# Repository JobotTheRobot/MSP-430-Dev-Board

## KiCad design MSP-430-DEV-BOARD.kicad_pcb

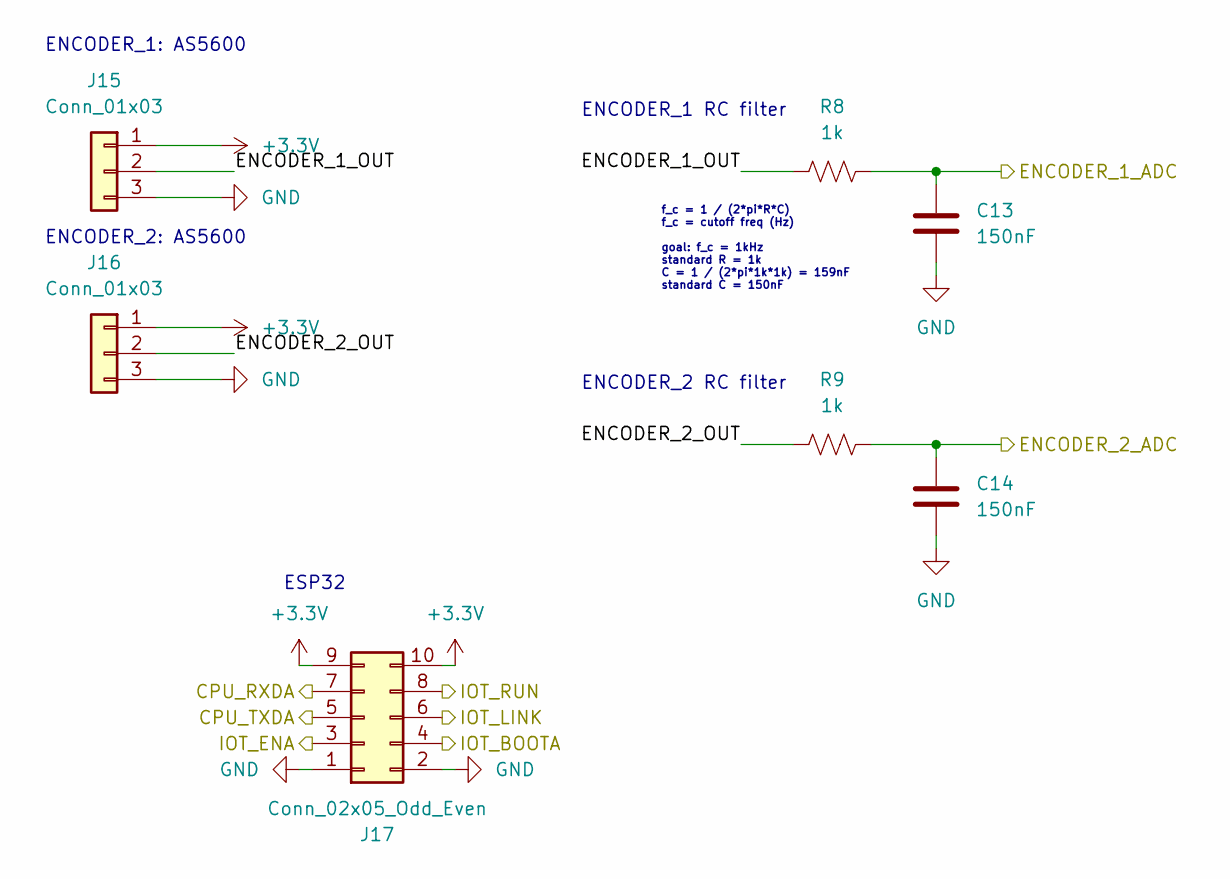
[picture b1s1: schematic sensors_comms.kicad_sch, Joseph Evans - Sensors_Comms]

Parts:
C13, C14: 150nF; C_0603_1608Metric
J15, J16: Conn_01x03; PinHeader_1x03_P2.54mm_Vertical
J17: Conn_02x05_Odd_Even; PinHeader_2x05_P2.54mm_Vertical
R8, R9: 1k; R_0603_1608Metric_Pad0.98x0.95mm_HandSolder

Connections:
+3.3V: J15.1, J16.1, J17.9, J17.10; also elsewhere on the board
/Processor/P1.0: C13.1, R8.2; also elsewhere on the board
/Processor/P1.1: C14.1, R9.2; also elsewhere on the board
/Processor/P1.2: J17.3; also elsewhere on the board
/Processor/P1.3: J17.8; also elsewhere on the board
/Processor/P1.4: J17.6; also elsewhere on the board
/Processor/P1.5: J17.4; also elsewhere on the board
/Processor/P1.6: J17.7; also elsewhere on the board
/Processor/P1.7: J17.5; also elsewhere on the board
/Sensors_Comms/ENCODER_1_OUT: J15.2, R8.1
/Sensors_Comms/ENCODER_2_OUT: J16.2, R9.1
GND: C13.2, C14.2, J15.3, J16.3, J17.1, J17.2; also elsewhere on the board

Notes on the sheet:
ENCODER_1: AS5600
ENCODER_2 RC filter
ENCODER_1 RC filter
ENCODER_2: AS5600
ESP32
f_c = 1 / (2*pi*R*C) f_c = cutoff freq (Hz) goal: f_c = 1kHz standard R = 1k C = 1 / (2*pi*1k*1k) = 159nF standard C = 150nF

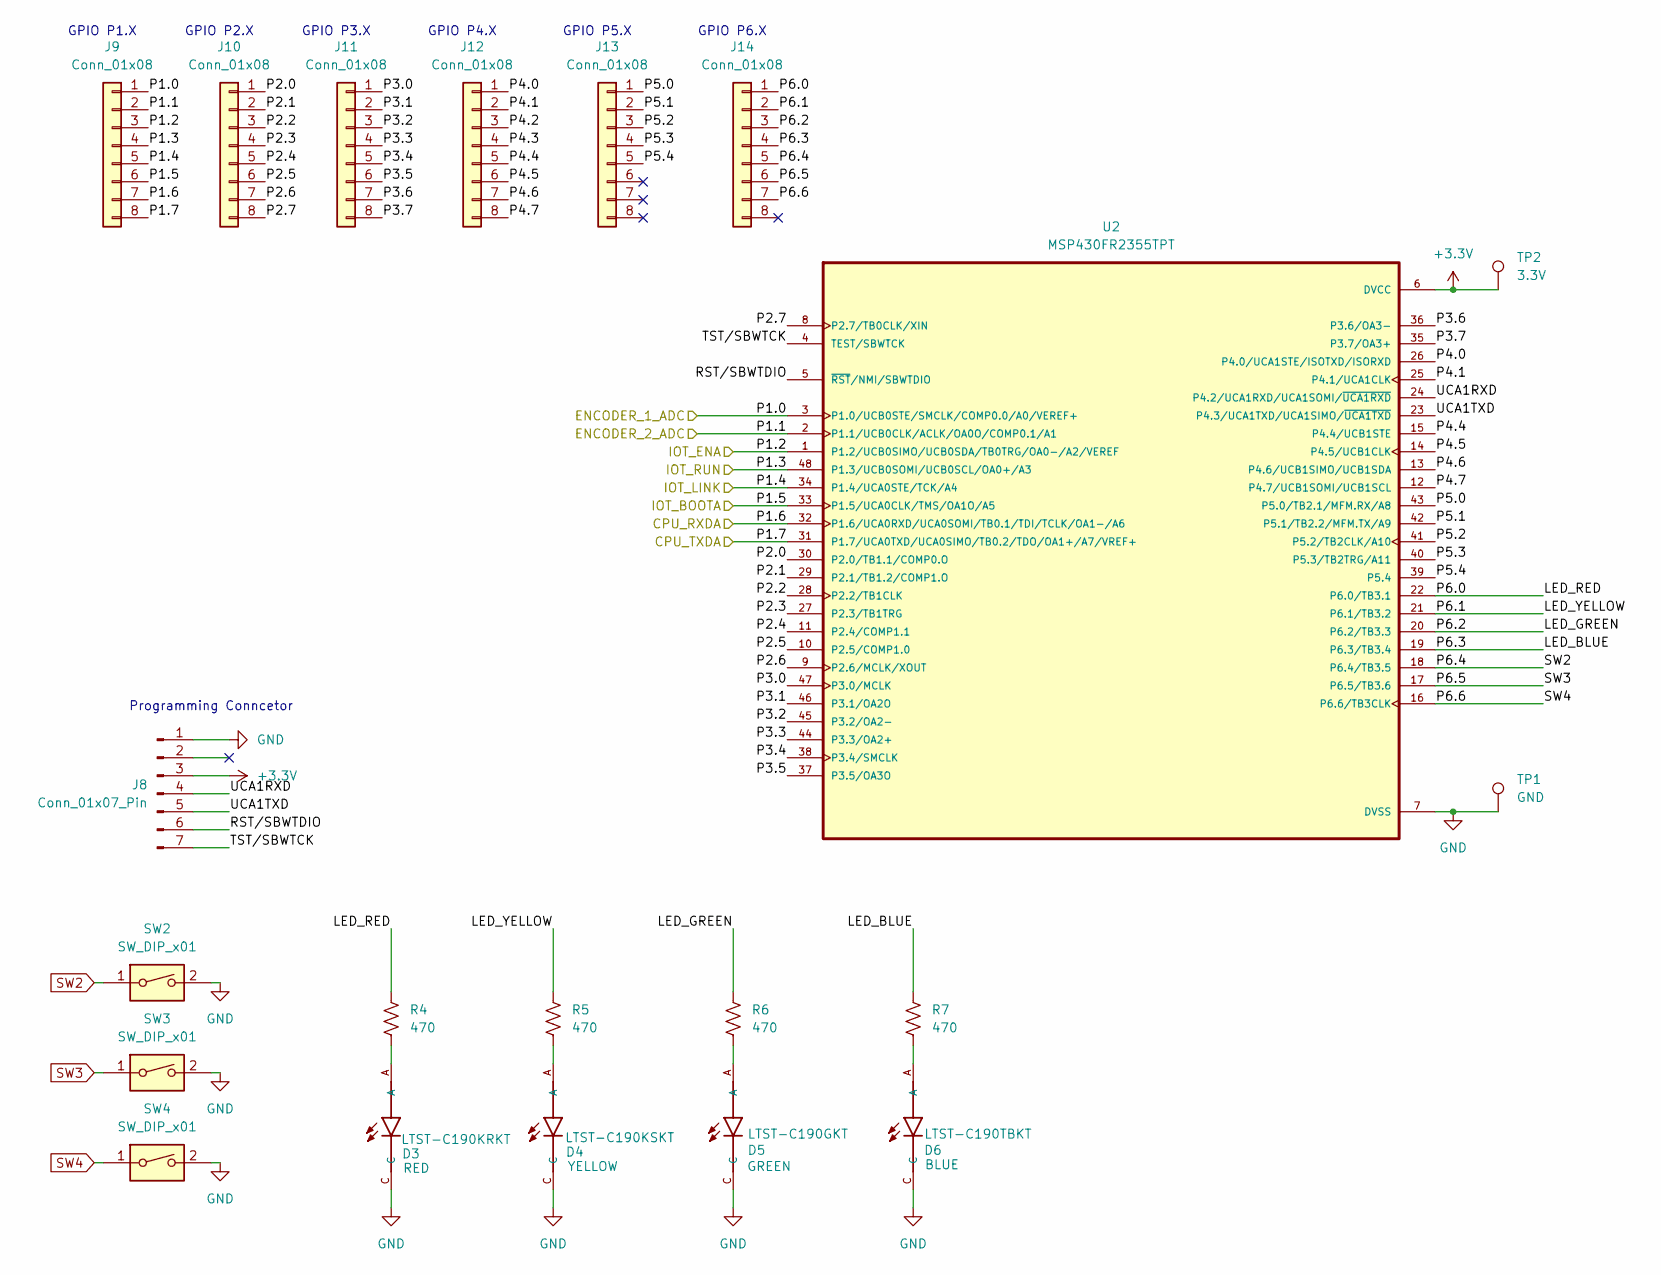
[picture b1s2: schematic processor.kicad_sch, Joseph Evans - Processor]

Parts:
D3: LTST-C190KRKT; LEDM1608X80; DigiKey_Part_Number 160-1436-1-ND
D4: LTST-C190KSKT; LEDM1608X80
D5: LTST-C190GKT; LEDM1608X80
D6: LTST-C190TBKT; LEDM1608X80
J8: Conn_01x07_Pin; PinHeader_1x07_P1.27mm_Vertical
J9, J10, J11, J12, J13, J14: Conn_01x08; PinHeader_1x08_P2.54mm_Vertical
R4, R5, R6, R7: 470; R_0603_1608Metric_Pad0.98x0.95mm_HandSolder
SW2, SW3, SW4: SW_DIP_x01; SW_Push_1P1T_NO_CK_KSC9xxG
TP1: GND; TestPoint_Pad_D2.0mm
TP2: 3.3V; TestPoint_Pad_D2.0mm
U2: MSP430FR2355TPT; QFP50P900X900X160-48N; DigiKey_Part_Number 296-50260-ND

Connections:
+3.3V: J8.3, TP2.1 (1_1), U2.6 (DVCC); also elsewhere on the board
/Processor/LED_BLUE: J14.4, R7.1, U2.19 (P6.3/TB3.4)
/Processor/LED_GREEN: J14.3, R6.1, U2.20 (P6.2/TB3.3)
/Processor/LED_RED: J14.1, R4.1, U2.22 (P6.0/TB3.1)
/Processor/LED_YELLOW: J14.2, R5.1, U2.21 (P6.1/TB3.2)
/Processor/P1.0: J9.1, U2.3 (P1.0/UCB0STE/SMCLK/COMP0.0/A0/VEREF+); also elsewhere on the board
/Processor/P1.1: J9.2, U2.2 (P1.1/UCB0CLK/ACLK/OA0O/COMP0.1/A1); also elsewhere on the board
/Processor/P1.2: J9.3, U2.1 (P1.2/UCB0SIMO/UCB0SDA/TB0TRG/OA0-/A2/VE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); also elsewhere on the board
/Processor/P1.3: J9.4, U2.48 (P1.3/UCB0SOMI/UCB0SCL/OA0+/A3); also elsewhere on the board
/Processor/P1.4: J9.5, U2.34 (P1.4/UCA0STE/TCK/A4); also elsewhere on the board
/Processor/P1.5: J9.6, U2.33 (P1.5/UCA0CLK/TMS/OA1O/A5); also elsewhere on the board
/Processor/P1.6: J9.7, U2.32 (P1.6/UCA0RXD/UCA0SOMI/TB0.1/TDI/TCLK/OA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); also elsewhere on the board
/Processor/P1.7: J9.8, U2.31 (P1.7/UCA0TXD/UCA0SIMO/TB0.2/TDO/OA1+/A7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); also elsewhere on the board
/Processor/P2.0: J10.1, U2.30 (P2.0/TB1.1/COMP0.O)
/Processor/P2.1: J10.2, U2.29 (P2.1/TB1.2/COMP1.O)
/Processor/P2.2: J10.3, U2.28 (P2.2/TB1CLK)
/Processor/P2.3: J10.4, U2.27 (P2.3/TB1TRG)
/Processor/P2.4: J10.5, U2.11 (P2.4/COMP1.1)
/Processor/P2.5: J10.6, U2.10 (P2.5/COMP1.0)
/Processor/P2.6: J10.7, U2.9 (P2.6/MCLK/XOUT)
/Processor/P2.7: J10.8, U2.8 (P2.7/TB0CLK/XIN)
/Processor/P3.0: J11.1, U2.47 (P3.0/MCLK)
/Processor/P3.1: J11.2, U2.46 (P3.1/OA2O)
/Processor/P3.2: J11.3, U2.45 (P3.2/OA2-)
/Processor/P3.3: J11.4, U2.44 (P3.3/OA2+)
/Processor/P3.4: J11.5, U2.38 (P3.4/SMCLK)
/Processor/P3.5: J11.6, U2.37 (P3.5/OA3O)
/Processor/P3.6: J11.7, U2.36 (P3.6/OA3-)
/Processor/P3.7: J11.8, U2.35 (P3.7/OA3+)
/Processor/P4.0: J12.1, U2.26 (P4.0/UCA1STE/ISOTXD/ISORXD)
/Processor/P4.1: J12.2, U2.25 (P4.1/UCA1CLK)
/Processor/P4.2: J12.3
/Processor/P4.3: J12.4
/Processor/P4.4: J12.5, U2.15 (P4.4/UCB1STE)
/Processor/P4.5: J12.6, U2.14 (P4.5/UCB1CLK)
/Processor/P4.6: J12.7, U2.13 (P4.6/UCB1SIMO/UCB1SDA)
/Processor/P4.7: J12.8, U2.12 (P4.7/UCB1SOMI/UCB1SCL)
/Processor/P5.0: J13.1, U2.43 (P5.0/TB2.1/MFM.RX/A8)
/Processor/P5.1: J13.2, U2.42 (P5.1/TB2.2/MFM.TX/A9)
/Processor/P5.2: J13.3, U2.41 (P5.2/TB2CLK/A10)
/Processor/P5.3: J13.4, U2.40 (P5.3/TB2TRG/A11)
/Processor/P5.4: J13.5, U2.39 (P5.4)
/Processor/RST/SBWTDIO: J8.6, U2.5 (~RST/NMI/SBWTDIO)
/Processor/TST/SBWTCK: J8.7, U2.4 (TEST/SBWTCK)
/Processor/UCA1RXD: J8.4, U2.24 (P4.2/UCA1RXD/UCA1SOMI/~UCA1RXD)
/Processor/UCA1TXD: J8.5, U2.23 (P4.3/UCA1TXD/UCA1SIMO/~UCA1TXD)
GND: D3.C, D4.C, D5.C, D6.C, J8.1, SW2.2, SW3.2, SW4.2, TP1.1 (1_1), U2.7 (DVSS); also elsewhere on the board
unnamed: D3.A, R4.2
unnamed: D4.A, R5.2
unnamed: D5.A, R6.2
unnamed: D6.A, R7.2
SW2: J14.5, SW2.1, U2.18 (P6.4/TB3.5)
SW3: J14.6, SW3.1, U2.17 (P6.5/TB3.6)
SW4: J14.7, SW4.1, U2.16 (P6.6/TB3CLK)

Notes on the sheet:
GPIO P3.X
Programming Conncetor
GPIO P4.X
GPIO P1.X
GPIO P5.X
GPIO P2.X
GPIO P6.X

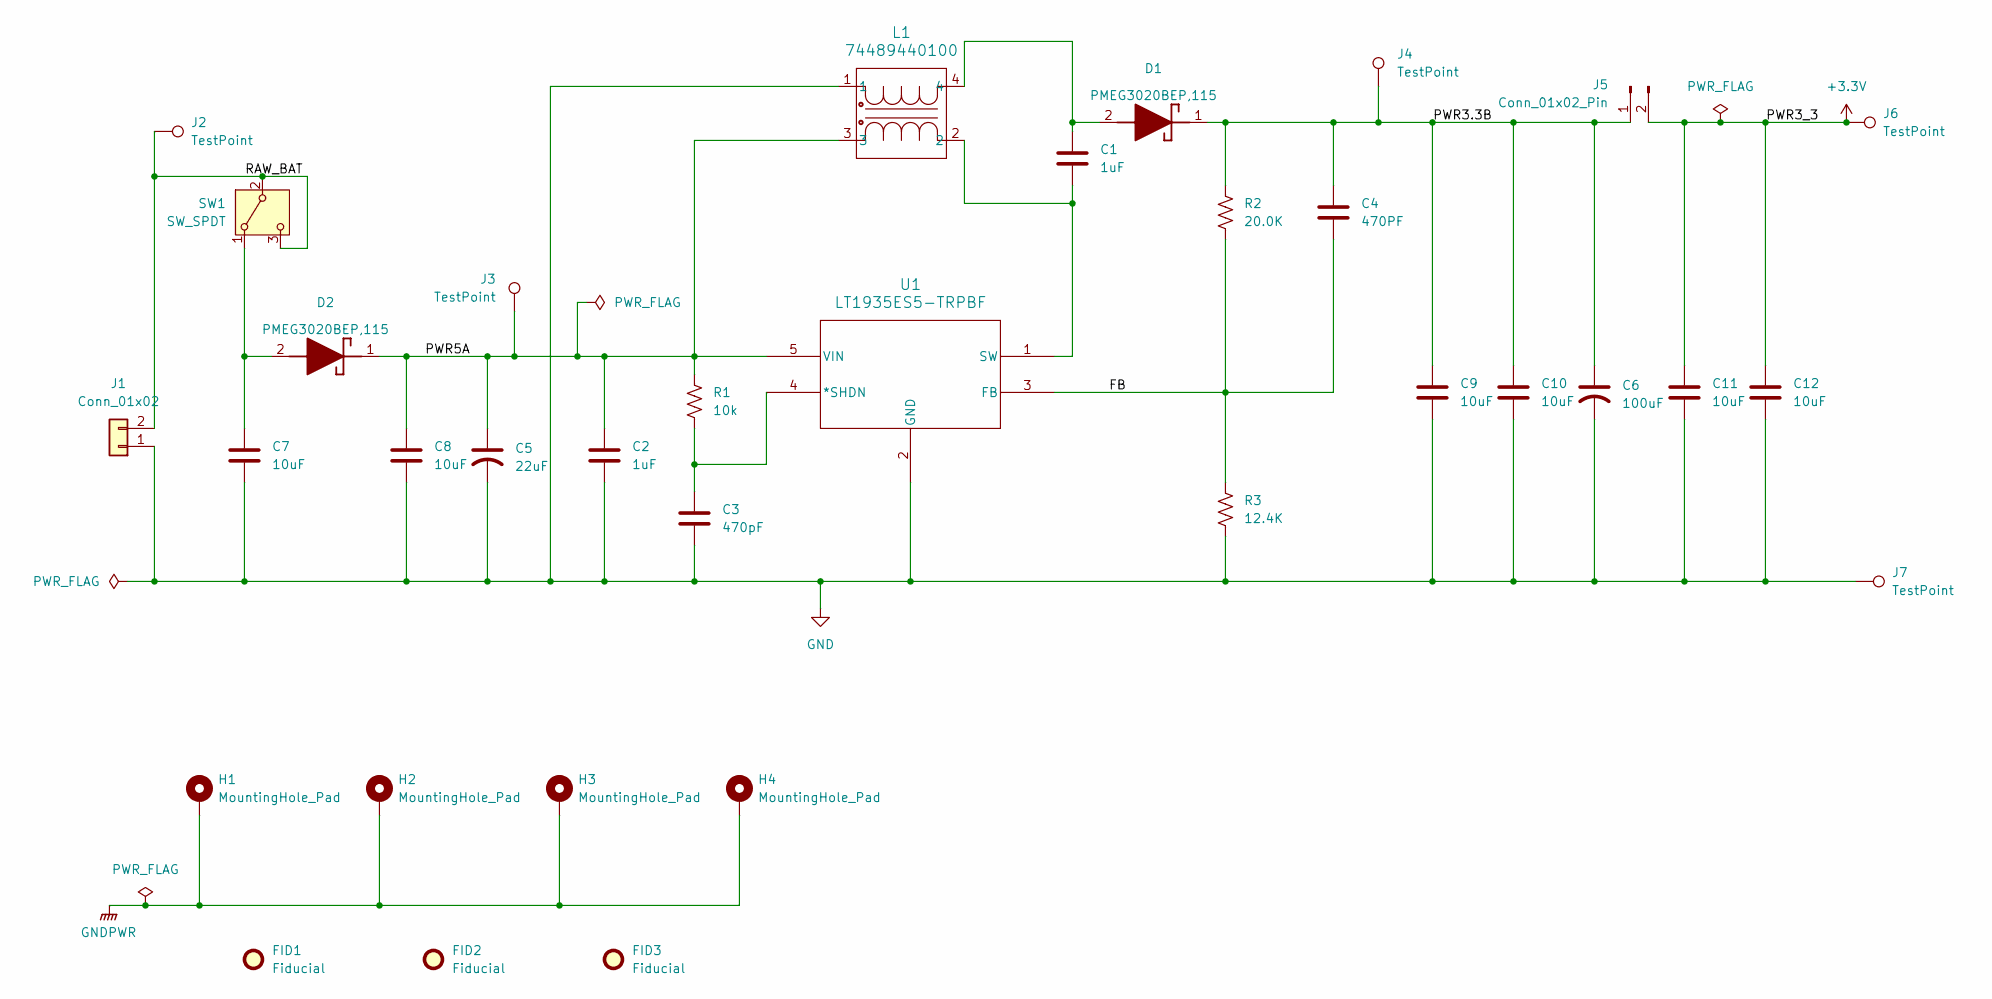
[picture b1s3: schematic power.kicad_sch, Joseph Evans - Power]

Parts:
C1: 1uF; C_1206_3216Metric_Pad1.33x1.80mm_HandSolder
C2: 1uF; C_0603_1608Metric
C3: 470pF; C_0603_1608Metric
C4: 470PF; C_0603_1608Metric
C5: 22uF; CP_EIA-7132-20_AVX-U
C6: 100uF; CP_EIA-7343-40_Kemet-Y
C7, C8, C9, C10, C11, C12: 10uF; C_0603_1608Metric
D1, D2: PMEG3020BEP,115; SODFL4725X110N; Mouser Part Number 771-PMEG3020BEP-115
FID1, FID2, FID3: Fiducial; Fiducial_1.5mm_Mask3mm
H1, H2, H3, H4: MountingHole_Pad; MountingHole_3.2mm_M3_Pad_TopBottom
J1: Conn_01x02; PinHeader_1x02_P2.54mm_Horizontal
J2, J3, J4, J6, J7: TestPoint; TestPoint_Loop_D1.80mm_Drill1.0mm_Beaded
J5: Conn_01x02_Pin; PinHeader_1x02_P2.54mm_Vertical
L1: 74489440100; WE-TDC_8038
R1: 10k; R_0603_1608Metric_Pad0.98x0.95mm_HandSolder
R2: 20.0K; R_0603_1608Metric_Pad0.98x0.95mm_HandSolder
R3: 12.4K; R_0603_1608Metric_Pad0.98x0.95mm_HandSolder
SW1: SW_SPDT; SW_Slide_SPDT_Angled_CK_OS102011MA1Q
U1: LT1935ES5-TRPBF; S_5_ADI

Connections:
+3.3V: C11.1, C12.1, J5.2, J6.1 (1_1); also elsewhere on the board
/Power/FB: C4.2, R2.2, R3.1, U1.3 (FB)
/Power/PWR3.3B: C4.1, C6.1, C9.1, C10.1, D1.1 (K), J4.1 (1_1), J5.1, R2.1
/Power/PWR5A: C2.1, C5.1, C8.1, D2.1 (K), J3.1 (1_1), L1.3, R1.1, U1.5 (VIN)
/Power/RAW_BAT: J1.2, J2.1 (1_1), SW1.2 (B), SW1.3 (C)
GND: C2.2, C3.2, C5.2, C6.2, C7.2, C8.2, C9.2, C10.2, C11.2, C12.2, J1.1, J7.1 (1_1), L1.1, R3.2, U1.2 (GND); also elsewhere on the board
GNDPWR: H1.1 (1_1), H2.1 (1_1), H3.1 (1_1), H4.1 (1_1)
unnamed: C1.1, D1.2 (A), L1.4
unnamed: C7.1, D2.2 (A), SW1.1 (A)
unnamed: C3.1, R1.2, U1.4 (*SHDN)
unnamed: C1.2, L1.2, U1.1 (SW)

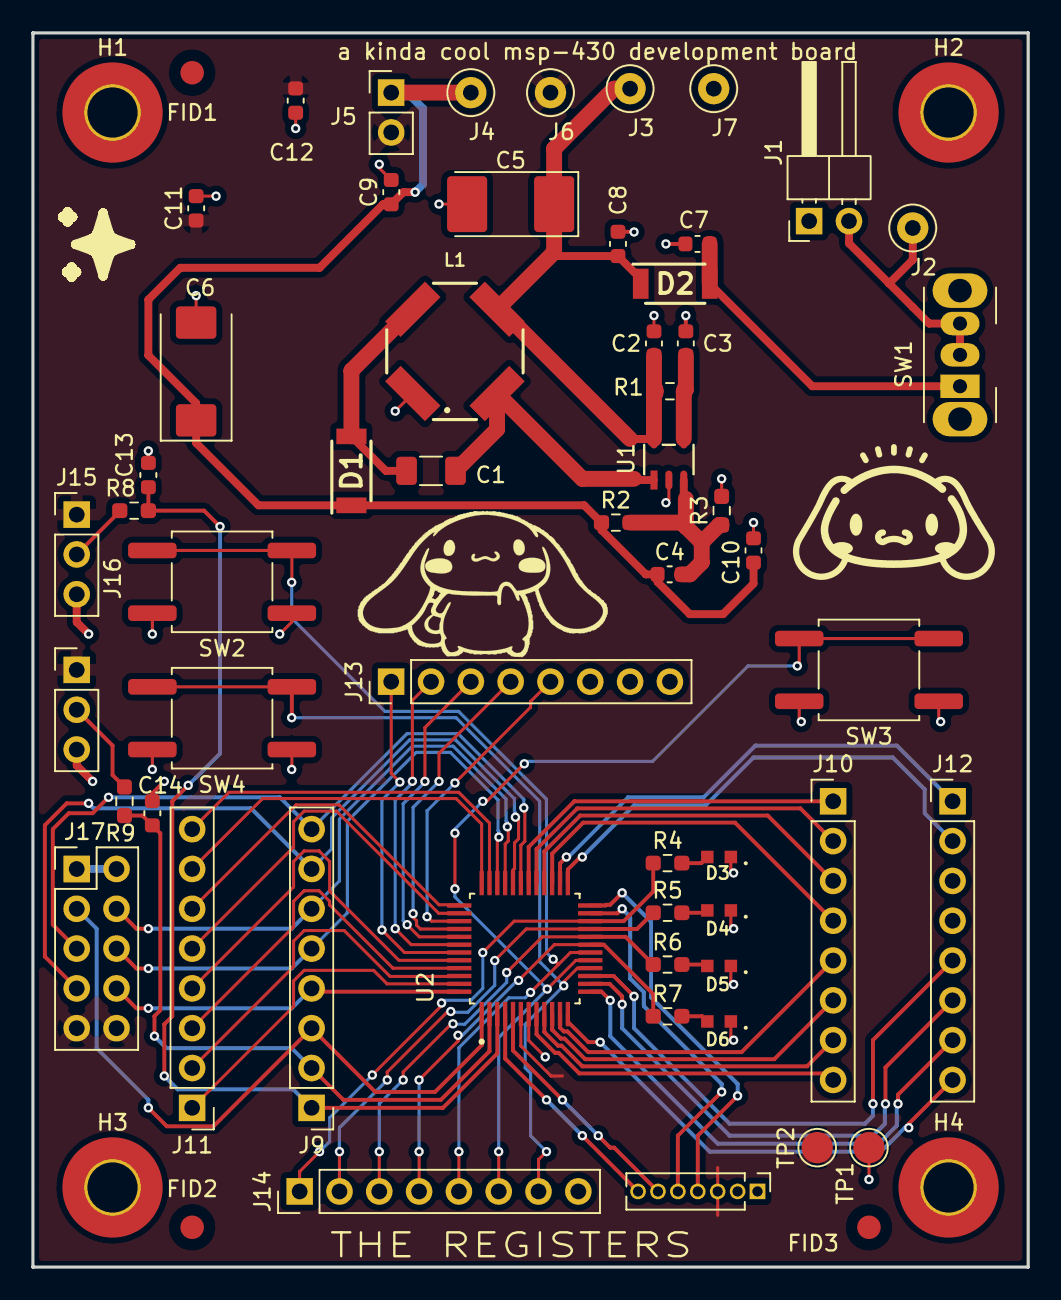
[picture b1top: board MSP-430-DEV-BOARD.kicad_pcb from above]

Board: 2 copper layers, 63.5 x 78.7 mm, 62 parts (0 on the bottom side), 63 nets.
